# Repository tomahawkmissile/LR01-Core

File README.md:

# LR01-Core
Core controller of the LR-01 hybrid drone. Controls rotors, critical cooling, battery charge/discharge controllers and realtime sensors.

Aircraft specifications will be posted in another repository.
***Note: these files are about 95% complete.***

Features:
- TI AM3354 Arm Cortex-A8
- 512MB DDR3 (800MHz)
- HDMI out
- 1 Gigabit ethernet
- 2 USB 2.0
- 2 16GB eMCC flash
- 1 Application connector
- 12 layer PCB

***Note: this board may or may not function.***

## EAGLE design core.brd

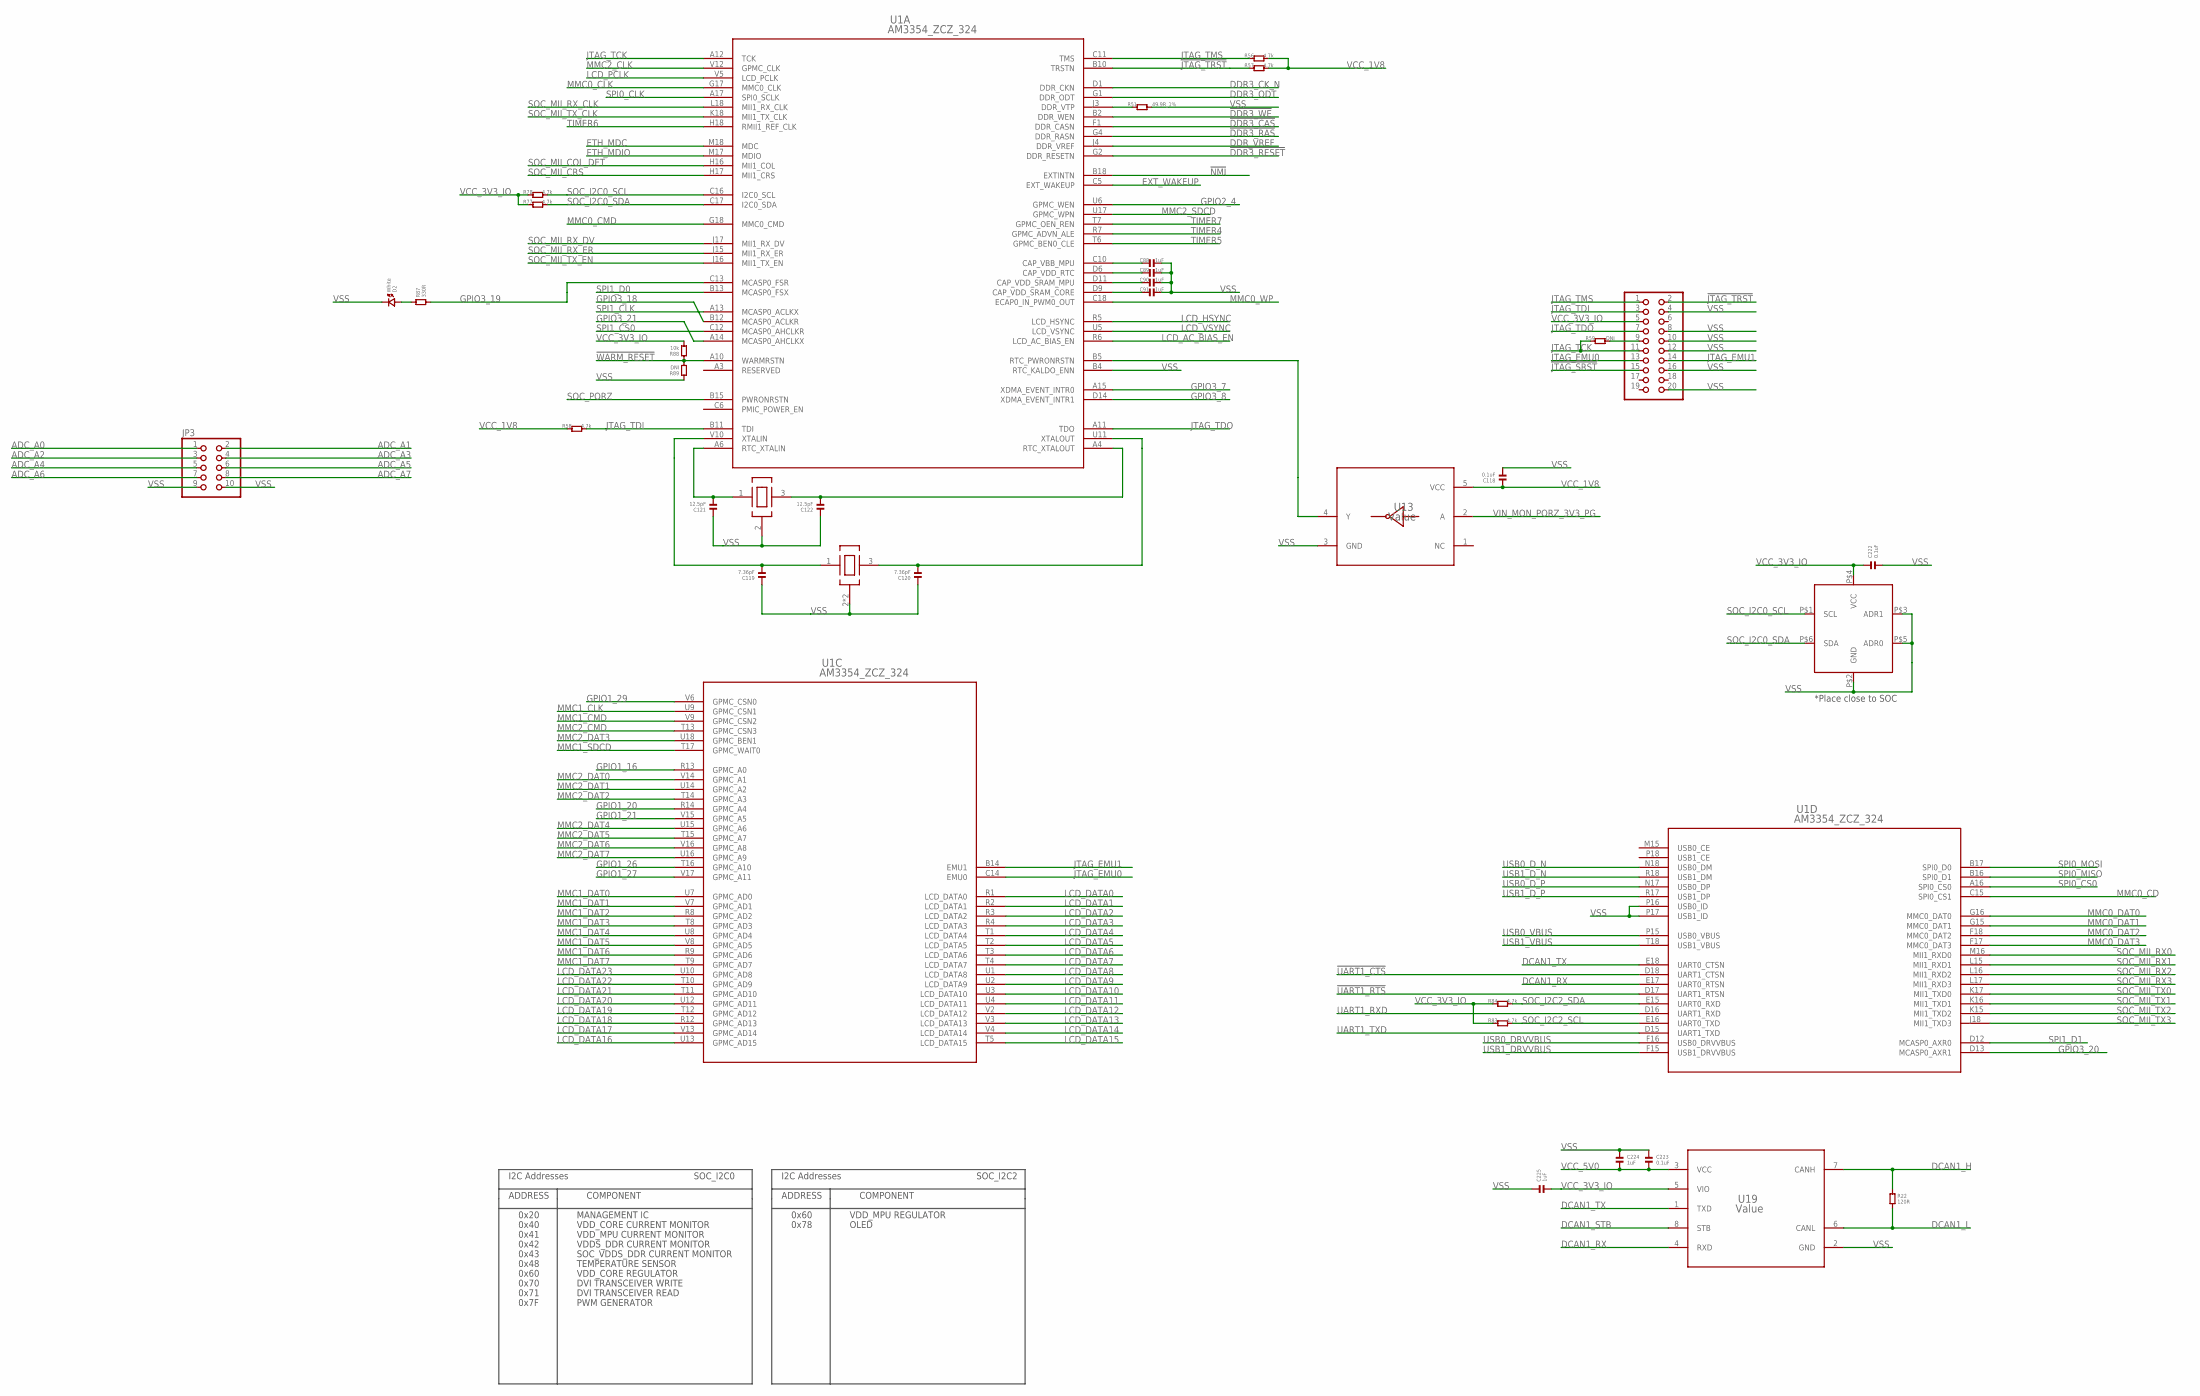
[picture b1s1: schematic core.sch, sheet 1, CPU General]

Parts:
C88, C89, C90, C91: 1uF; 0201
C118, C222, C223: 0.1uF; 0402
C119, C120: 7.36pF; 0402
C121, C122: 12.5pF; 0402
C224, C225: 1uF; 0402
D2: White; 0603.LED
JP1: PINHD-2X10; 2X10
JP3: PINHD-2X5; 2X05
R22: 120R; 0402
R51: 49.9R_1%; 0201
R56, R57, R58: 4.7k; 0603
R59, R89: DNI; 0402
R77, R78, R83, R84: 4.7k; 0402
R87: 330R; 0603
R88: 10k; 0402
U1: AM3354_ZCZ_324; ZCZ324
U13: Value; DCK0005A_N
U19: Value; D0008A_N
U$5: ECS-.327-12.5-1210B-N-TR; OSCCC120X100X35
U$6: NX3225SA-26.000000MHZ-G3; OSCCC320X250X70
U$9: TMP100; SOT23-6

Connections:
!DDR3_CAS: U1.F1 (DDR_CASN); also elsewhere on the board
!DDR3_RAS: U1.G4 (DDR_RASN); also elsewhere on the board
!DDR3_RESET: U1.G2 (DDR_RESETN); also elsewhere on the board
!DDR3_WE: U1.B2 (DDR_WEN); also elsewhere on the board
!JTAG_SRST: JP1.15
!JTAG_TRST: JP1.2, R57.1, U1.B10 (TRSTN); also elsewhere on the board
!NMI: U1.B18 (EXTINTN); also elsewhere on the board
!UART1_CTS: U1.D18 (UART1_CTSN); also elsewhere on the board
!UART1_RTS: U1.D17 (UART1_RTSN); also elsewhere on the board
!WARM_RESET: R88.1, R89.2, U1.A10 (WARMRSTN); also elsewhere on the board
ADC_A0: JP3.1; also elsewhere on the board
ADC_A1: JP3.2; also elsewhere on the board
ADC_A2: JP3.3; also elsewhere on the board
ADC_A3: JP3.4; also elsewhere on the board
ADC_A4: JP3.5; also elsewhere on the board
ADC_A5: JP3.6; also elsewhere on the board
ADC_A6: JP3.7; also elsewhere on the board
ADC_A7: JP3.8; also elsewhere on the board
DCAN1_H: R22.1, U19.7 (CANH); also elsewhere on the board
DCAN1_L: R22.2, U19.6 (CANL); also elsewhere on the board
DCAN1_RX: U1.E17 (UART0_RTSN), U19.4 (RXD)
DCAN1_STB: U19.8 (STB); also elsewhere on the board
DCAN1_TX: U1.E18 (UART0_CTSN), U19.1 (TXD)
DDR3_CK_N: U1.D1 (DDR_CKN); also elsewhere on the board
DDR3_ODT: U1.G1 (DDR_ODT); also elsewhere on the board
DDR_VREF: U1.J4 (DDR_VREF); also elsewhere on the board
ETH_MDC: U1.M18 (MDC); also elsewhere on the board
ETH_MDIO: U1.M17 (MDIO); also elsewhere on the board
EXT_WAKEUP: U1.C5 (EXT_WAKEUP); also elsewhere on the board
GPIO1_16: U1.R13 (GPMC_A0); also elsewhere on the board
GPIO1_20: U1.R14 (GPMC_A4); also elsewhere on the board
GPIO1_21: U1.V15 (GPMC_A5); also elsewhere on the board
GPIO1_26: U1.T16 (GPMC_A10); also elsewhere on the board
GPIO1_27: U1.V17 (GPMC_A11); also elsewhere on the board
GPIO1_29: U1.V6 (GPMC_CSN0); also elsewhere on the board
GPIO2_4: U1.U6 (GPMC_WEN); also elsewhere on the board
GPIO3_7: U1.A15 (XDMA_EVENT_INTR0); also elsewhere on the board
GPIO3_8: U1.D14 (XDMA_EVENT_INTR1); also elsewhere on the board
GPIO3_18: U1.B12 (MCASP0_ACLKR); also elsewhere on the board
GPIO3_19: R87.2, U1.C13 (MCASP0_FSR); also elsewhere on the board
GPIO3_20: U1.D13 (MCASP0_AXR1); also elsewhere on the board
GPIO3_21: U1.A14 (MCASP0_AHCLKX); also elsewhere on the board
JTAG_EMU0: JP1.13, U1.C14 (EMU0)
JTAG_EMU1: JP1.14, U1.B14 (EMU1)
JTAG_TCK: JP1.11, R59.1, U1.A12 (TCK)
JTAG_TDI: JP1.3, R58.2, U1.B11 (TDI)
JTAG_TDO: JP1.7, U1.A11 (TDO)
JTAG_TMS: JP1.1, R56.1, U1.C11 (TMS)
LCD_AC_BIAS_EN: U1.R6 (LCD_AC_BIAS_EN); also elsewhere on the board
LCD_DATA0: U1.R1 (LCD_DATA0); also elsewhere on the board
LCD_DATA1: U1.R2 (LCD_DATA1); also elsewhere on the board
LCD_DATA2: U1.R3 (LCD_DATA2); also elsewhere on the board
LCD_DATA3: U1.R4 (LCD_DATA3); also elsewhere on the board
LCD_DATA4: U1.T1 (LCD_DATA4); also elsewhere on the board
LCD_DATA5: U1.T2 (LCD_DATA5); also elsewhere on the board
LCD_DATA6: U1.T3 (LCD_DATA6); also elsewhere on the board
LCD_DATA7: U1.T4 (LCD_DATA7); also elsewhere on the board
LCD_DATA8: U1.U1 (LCD_DATA8); also elsewhere on the board
LCD_DATA9: U1.U2 (LCD_DATA9); also elsewhere on the board
LCD_DATA10: U1.U3 (LCD_DATA10); also elsewhere on the board
LCD_DATA11: U1.U4 (LCD_DATA11); also elsewhere on the board
LCD_DATA12: U1.V2 (LCD_DATA12); also elsewhere on the board
LCD_DATA13: U1.V3 (LCD_DATA13); also elsewhere on the board
LCD_DATA14: U1.V4 (LCD_DATA14); also elsewhere on the board
LCD_DATA15: U1.T5 (LCD_DATA15); also elsewhere on the board
LCD_DATA16: U1.U13 (GPMC_AD15); also elsewhere on the board
LCD_DATA17: U1.V13 (GPMC_AD14); also elsewhere on the board
LCD_DATA18: U1.R12 (GPMC_AD13); also elsewhere on the board
LCD_DATA19: U1.T12 (GPMC_AD12); also elsewhere on the board
LCD_DATA20: U1.U12 (GPMC_AD11); also elsewhere on the board
LCD_DATA21: U1.T11 (GPMC_AD10); also elsewhere on the board
LCD_DATA22: U1.T10 (GPMC_AD9); also elsewhere on the board
LCD_DATA23: U1.U10 (GPMC_AD8); also elsewhere on the board
LCD_HSYNC: U1.R5 (LCD_HSYNC); also elsewhere on the board
LCD_PCLK: U1.V5 (LCD_PCLK); also elsewhere on the board
LCD_VSYNC: U1.U5 (LCD_VSYNC); also elsewhere on the board
MMC0_CD: U1.C15 (SPI0_CS1); also elsewhere on the board
MMC0_CLK: U1.G17 (MMC0_CLK); also elsewhere on the board
MMC0_CMD: U1.G18 (MMC0_CMD); also elsewhere on the board
MMC0_DAT0: U1.G16 (MMC0_DAT0); also elsewhere on the board
MMC0_DAT1: U1.G15 (MMC0_DAT1); also elsewhere on the board
MMC0_DAT2: U1.F18 (MMC0_DAT2); also elsewhere on the board
MMC0_DAT3: U1.F17 (MMC0_DAT3); also elsewhere on the board
MMC0_WP: U1.C18 (ECAP0_IN_PWM0_OUT); also elsewhere on the board
MMC1_CLK: U1.U9 (GPMC_CSN1); also elsewhere on the board
MMC1_CMD: U1.V9 (GPMC_CSN2); also elsewhere on the board
MMC1_DAT0: U1.U7 (GPMC_AD0); also elsewhere on the board
MMC1_DAT1: U1.V7 (GPMC_AD1); also elsewhere on the board
MMC1_DAT2: U1.R8 (GPMC_AD2); also elsewhere on the board
MMC1_DAT3: U1.T8 (GPMC_AD3); also elsewhere on the board
MMC1_DAT4: U1.U8 (GPMC_AD4); also elsewhere on the board
MMC1_DAT5: U1.V8 (GPMC_AD5); also elsewhere on the board
MMC1_DAT6: U1.R9 (GPMC_AD6); also elsewhere on the board
MMC1_DAT7: U1.T9 (GPMC_AD7); also elsewhere on the board
MMC1_SDCD: U1.T17 (GPMC_WAIT0)
MMC2_CLK: U1.V12 (GPMC_CLK); also elsewhere on the board
MMC2_CMD: U1.T13 (GPMC_CSN3); also elsewhere on the board
MMC2_DAT0: U1.V14 (GPMC_A1); also elsewhere on the board
MMC2_DAT1: U1.U14 (GPMC_A2); also elsewhere on the board
MMC2_DAT2: U1.T14 (GPMC_A3); also elsewhere on the board
MMC2_DAT3: U1.U18 (GPMC_BEN1); also elsewhere on the board
MMC2_DAT4: U1.U15 (GPMC_A6); also elsewhere on the board
MMC2_DAT5: U1.T15 (GPMC_A7); also elsewhere on the board
MMC2_DAT6: U1.V16 (GPMC_A8); also elsewhere on the board
MMC2_DAT7: U1.U16 (GPMC_A9); also elsewhere on the board
MMC2_SDCD: U1.U17 (GPMC_WPN)
unnamed: JP1.9, R59.2
unnamed: C88.1, U1.C10 (CAP_VBB_MPU)
unnamed: C91.1, U1.D9 (CAP_VDD_SRAM_CORE)
unnamed: C90.1, U1.D11 (CAP_VDD_SRAM_MPU)
unnamed: U1.B5 (RTC_PWRONRSTN), U13.4 (Y)
unnamed: C121.2, U1.A6 (RTC_XTALIN), U$5.1 (XI)
unnamed: C122.2, U1.A4 (RTC_XTALOUT), U$5.3 (XO)
unnamed: C119.2, U1.V10 (XTALIN), U$6.1 (XI)
unnamed: C120.2, U1.U11 (XTALOUT), U$6.3 (XO)
unnamed: R51.1, U1.J3 (DDR_VTP)
unnamed: C89.1, U1.D6 (CAP_VDD_RTC)
unnamed: D2.P$1 (1), R87.1
SOC_I2C0_SCL: R78.2, U1.C16 (I2C0_SCL), U$9.P$1 (SCL); also elsewhere on the board
SOC_I2C0_SDA: R77.2, U1.C17 (I2C0_SDA), U$9.P$6 (SDA); also elsewhere on the board
SOC_I2C2_SCL: R83.2, U1.E16 (UART0_TXD); also elsewhere on the board
SOC_I2C2_SDA: R84.2, U1.E15 (UART0_RXD); also elsewhere on the board
SOC_MII_COL_DET: U1.H16 (MII1_COL); also elsewhere on the board
SOC_MII_CRS: U1.H17 (MII1_CRS); also elsewhere on the board
SOC_MII_RX0: U1.M16 (MII1_RXD0); also elsewhere on the board
SOC_MII_RX1: U1.L15 (MII1_RXD1); also elsewhere on the board
SOC_MII_RX2: U1.L16 (MII1_RXD2); also elsewhere on the board
SOC_MII_RX3: U1.L17 (MII1_RXD3); also elsewhere on the board
SOC_MII_RX_CLK: U1.L18 (MII1_RX_CLK); also elsewhere on the board
SOC_MII_RX_DV: U1.J17 (MII1_RX_DV); also elsewhere on the board
SOC_MII_RX_ER: U1.J15 (MII1_RX_ER); also elsewhere on the board
SOC_MII_TX0: U1.K17 (MII1_TXD0); also elsewhere on the board
SOC_MII_TX1: U1.K16 (MII1_TXD1); also elsewhere on the board
SOC_MII_TX2: U1.K15 (MII1_TXD2); also elsewhere on the board
SOC_MII_TX3: U1.J18 (MII1_TXD3); also elsewhere on the board
SOC_MII_TX_CLK: U1.K18 (MII1_TX_CLK); also elsewhere on the board
SOC_MII_TX_EN: U1.J16 (MII1_TX_EN); also elsewhere on the board
SOC_PORZ: U1.B15 (PWRONRSTN); also elsewhere on the board
SPI0_CLK: U1.A17 (SPI0_SCLK); also elsewhere on the board
SPI0_CS0: U1.A16 (SPI0_CS0); also elsewhere on the board
SPI0_MISO: U1.B16 (SPI0_D1); also elsewhere on the board
SPI0_MOSI: U1.B17 (SPI0_D0); also elsewhere on the board
SPI1_CLK: U1.A13 (MCASP0_ACLKX); also elsewhere on the board
SPI1_CS0: U1.C12 (MCASP0_AHCLKR); also elsewhere on the board
SPI1_D0: U1.B13 (MCASP0_FSX); also elsewhere on the board
SPI1_D1: U1.D12 (MCASP0_AXR0); also elsewhere on the board
TIMER4: U1.R7 (GPMC_ADVN_ALE); also elsewhere on the board
TIMER5: U1.T6 (GPMC_BEN0_CLE); also elsewhere on the board
TIMER6: U1.H18 (RMII1_REF_CLK); also elsewhere on the board
TIMER7: U1.T7 (GPMC_OEN_REN); also elsewhere on the board
UART1_RXD: U1.D16 (UART1_RXD); also elsewhere on the board
UART1_TXD: U1.D15 (UART1_TXD); also elsewhere on the board
USB0_DRVVBUS: U1.F16 (USB0_DRVVBUS); also elsewhere on the board
USB0_D_N: U1.N18 (USB0_DM); also elsewhere on the board
USB0_D_P: U1.N17 (USB0_DP); also elsewhere on the board
USB0_VBUS: U1.P15 (USB0_VBUS); also elsewhere on the board
USB1_DRVVBUS: U1.F15 (USB1_DRVVBUS); also elsewhere on the board
USB1_D_N: U1.R18 (USB1_DM); also elsewhere on the board
USB1_D_P: U1.R17 (USB1_DP); also elsewhere on the board
USB1_VBUS: U1.T18 (USB1_VBUS); also elsewhere on the board
VCC_1V8: C118.1, R56.2, R57.2, R58.1, U13.5 (VCC); also elsewhere on the board
VCC_3V3_IO: C222.1, C225.2, JP1.5, R77.1, R78.1, R83.1, R84.1, R88.2, U19.5 (VIO), U$9.P$4 (VCC); also elsewhere on the board
VCC_5V0: C223.2, C224.2, U19.3 (VCC); also elsewhere on the board
VIN_MON_PORZ_3V3_PG: U13.2 (A); also elsewhere on the board
VPP: U1.M5 (VPP)
VSS: C88.2, C89.2, C90.2, C91.2, C118.2, C119.1, C120.1, C121.1, C122.1, C222.2, C223.1, C224.1, C225.1, D2.P$2 (2), JP1.4, JP1.8, JP1.10, JP1.12, JP1.16, JP1.20, JP3.9, JP3.10, R51.2, R89.1, U1.B4 (RTC_KALDO_ENN), U1.P16 (USB0_ID), U1.P17 (USB1_ID), U13.3 (GND), U19.2 (GND), U$5.2 (VSS), U$6.2 (VSS), U$6.4 (VSS), U$9.P$2 (GND), U$9.P$3 (ADR1), U$9.P$5 (ADR0); also elsewhere on the board

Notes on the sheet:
I2C Addresses
0x20
MANAGEMENT IC
ADDRESS
COMPONENT
0x40
0x41
0x42
0x43
VDD_CORE CURRENT MONITOR
VDD_MPU CURRENT MONITOR
VDDS_DDR CURRENT MONITOR
SOC_VDDS_DDR CURRENT MONITOR
0x60
VDD_CORE REGULATOR
SOC_I2C0
VDD_MPU REGULATOR
SOC_I2C2
0x70
0x71
DVI TRANSCEIVER WRITE
DVI TRANSCEIVER READ
0x78
OLED
0x48
TEMPERATURE SENSOR
*Place close to SOC
0x7F
PWM GENERATOR

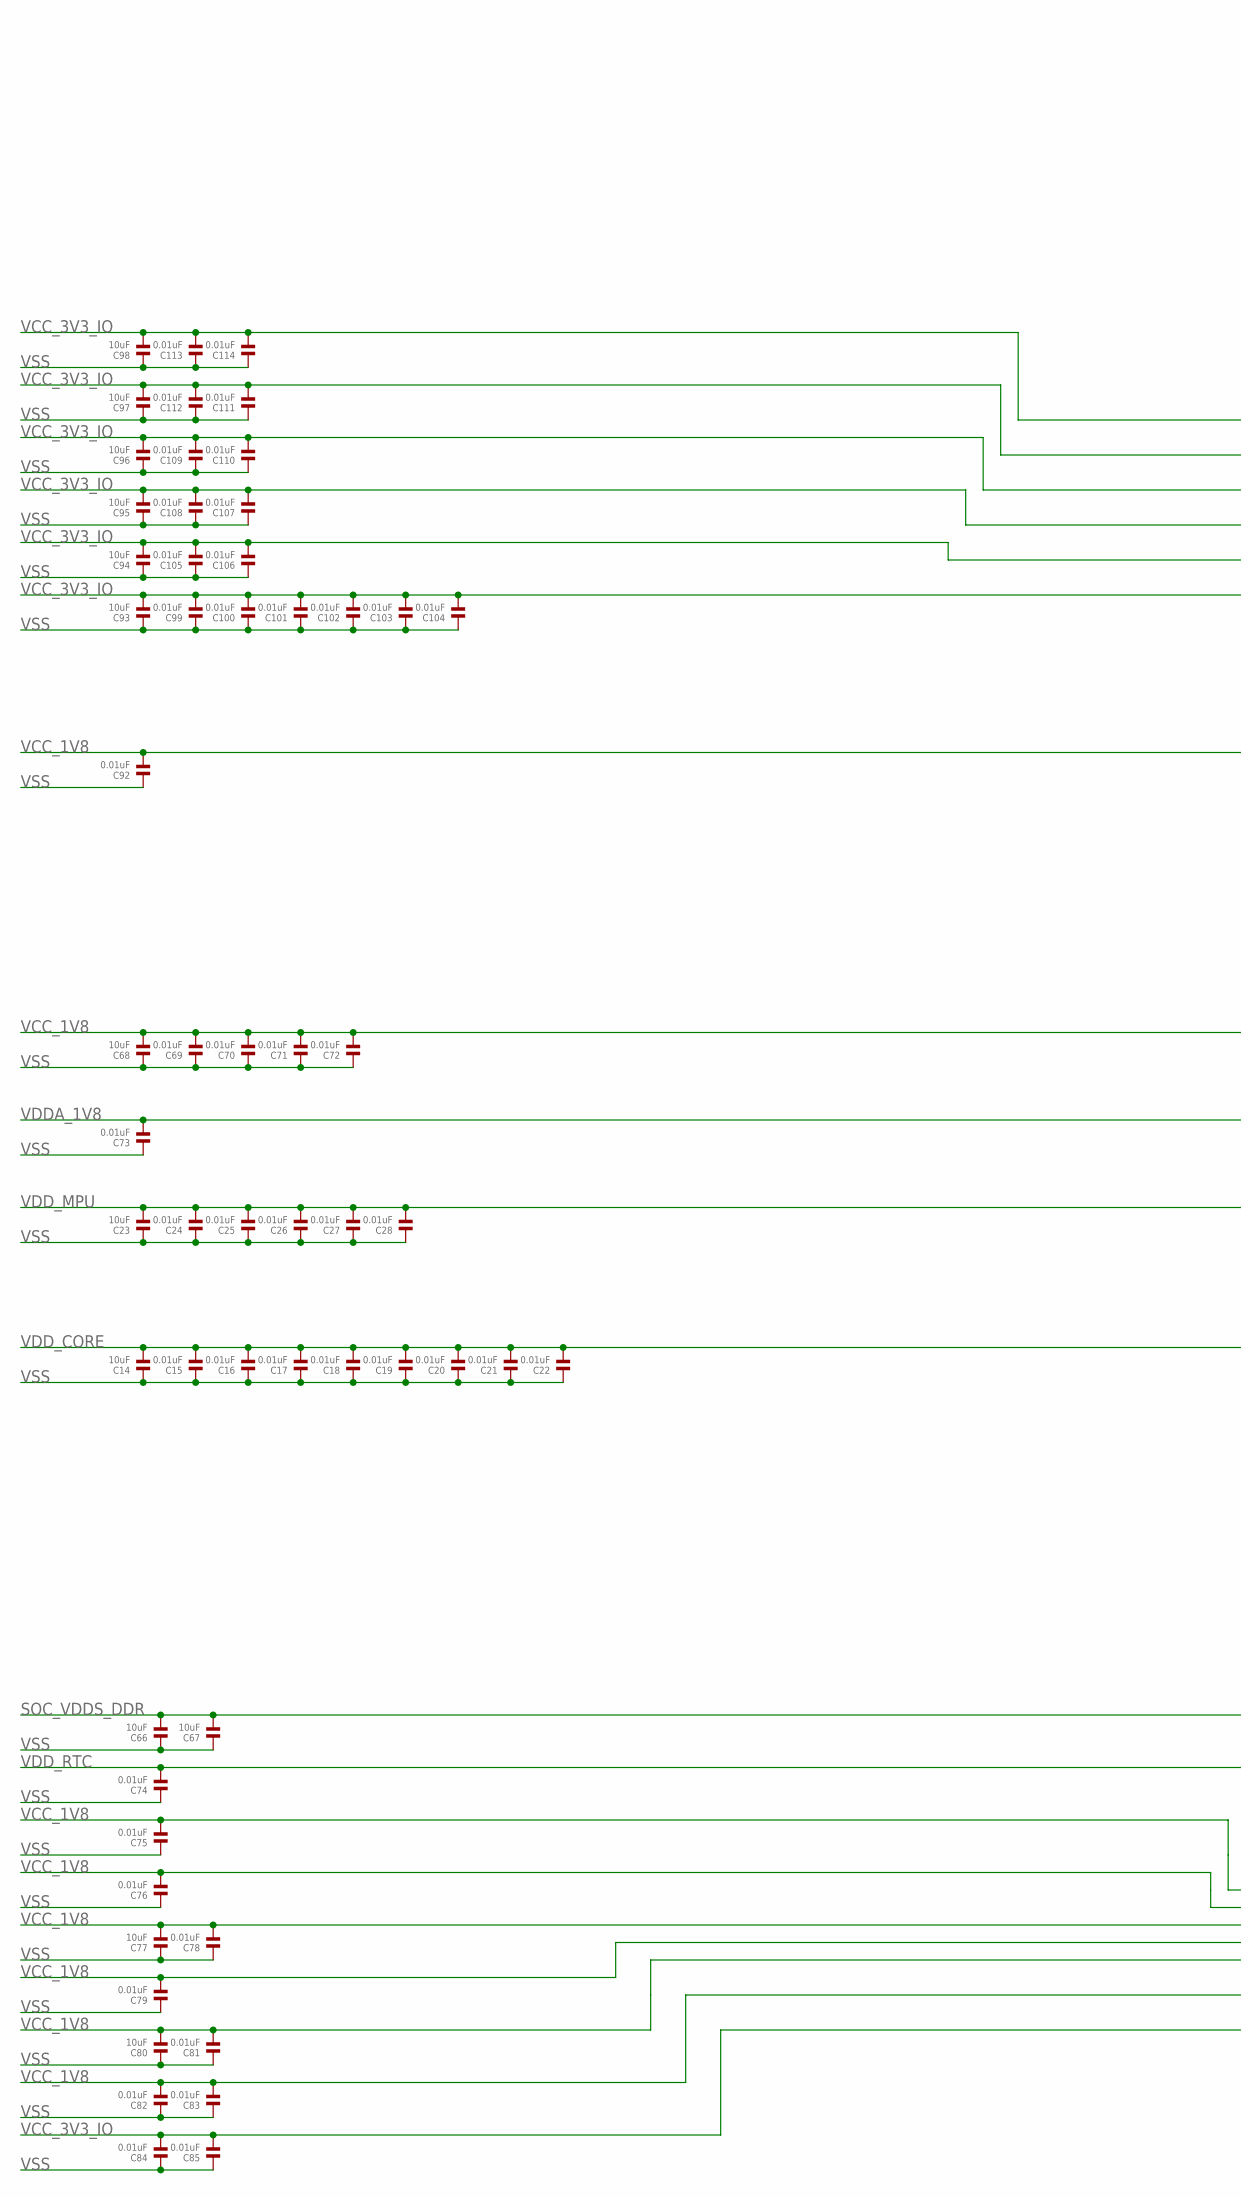
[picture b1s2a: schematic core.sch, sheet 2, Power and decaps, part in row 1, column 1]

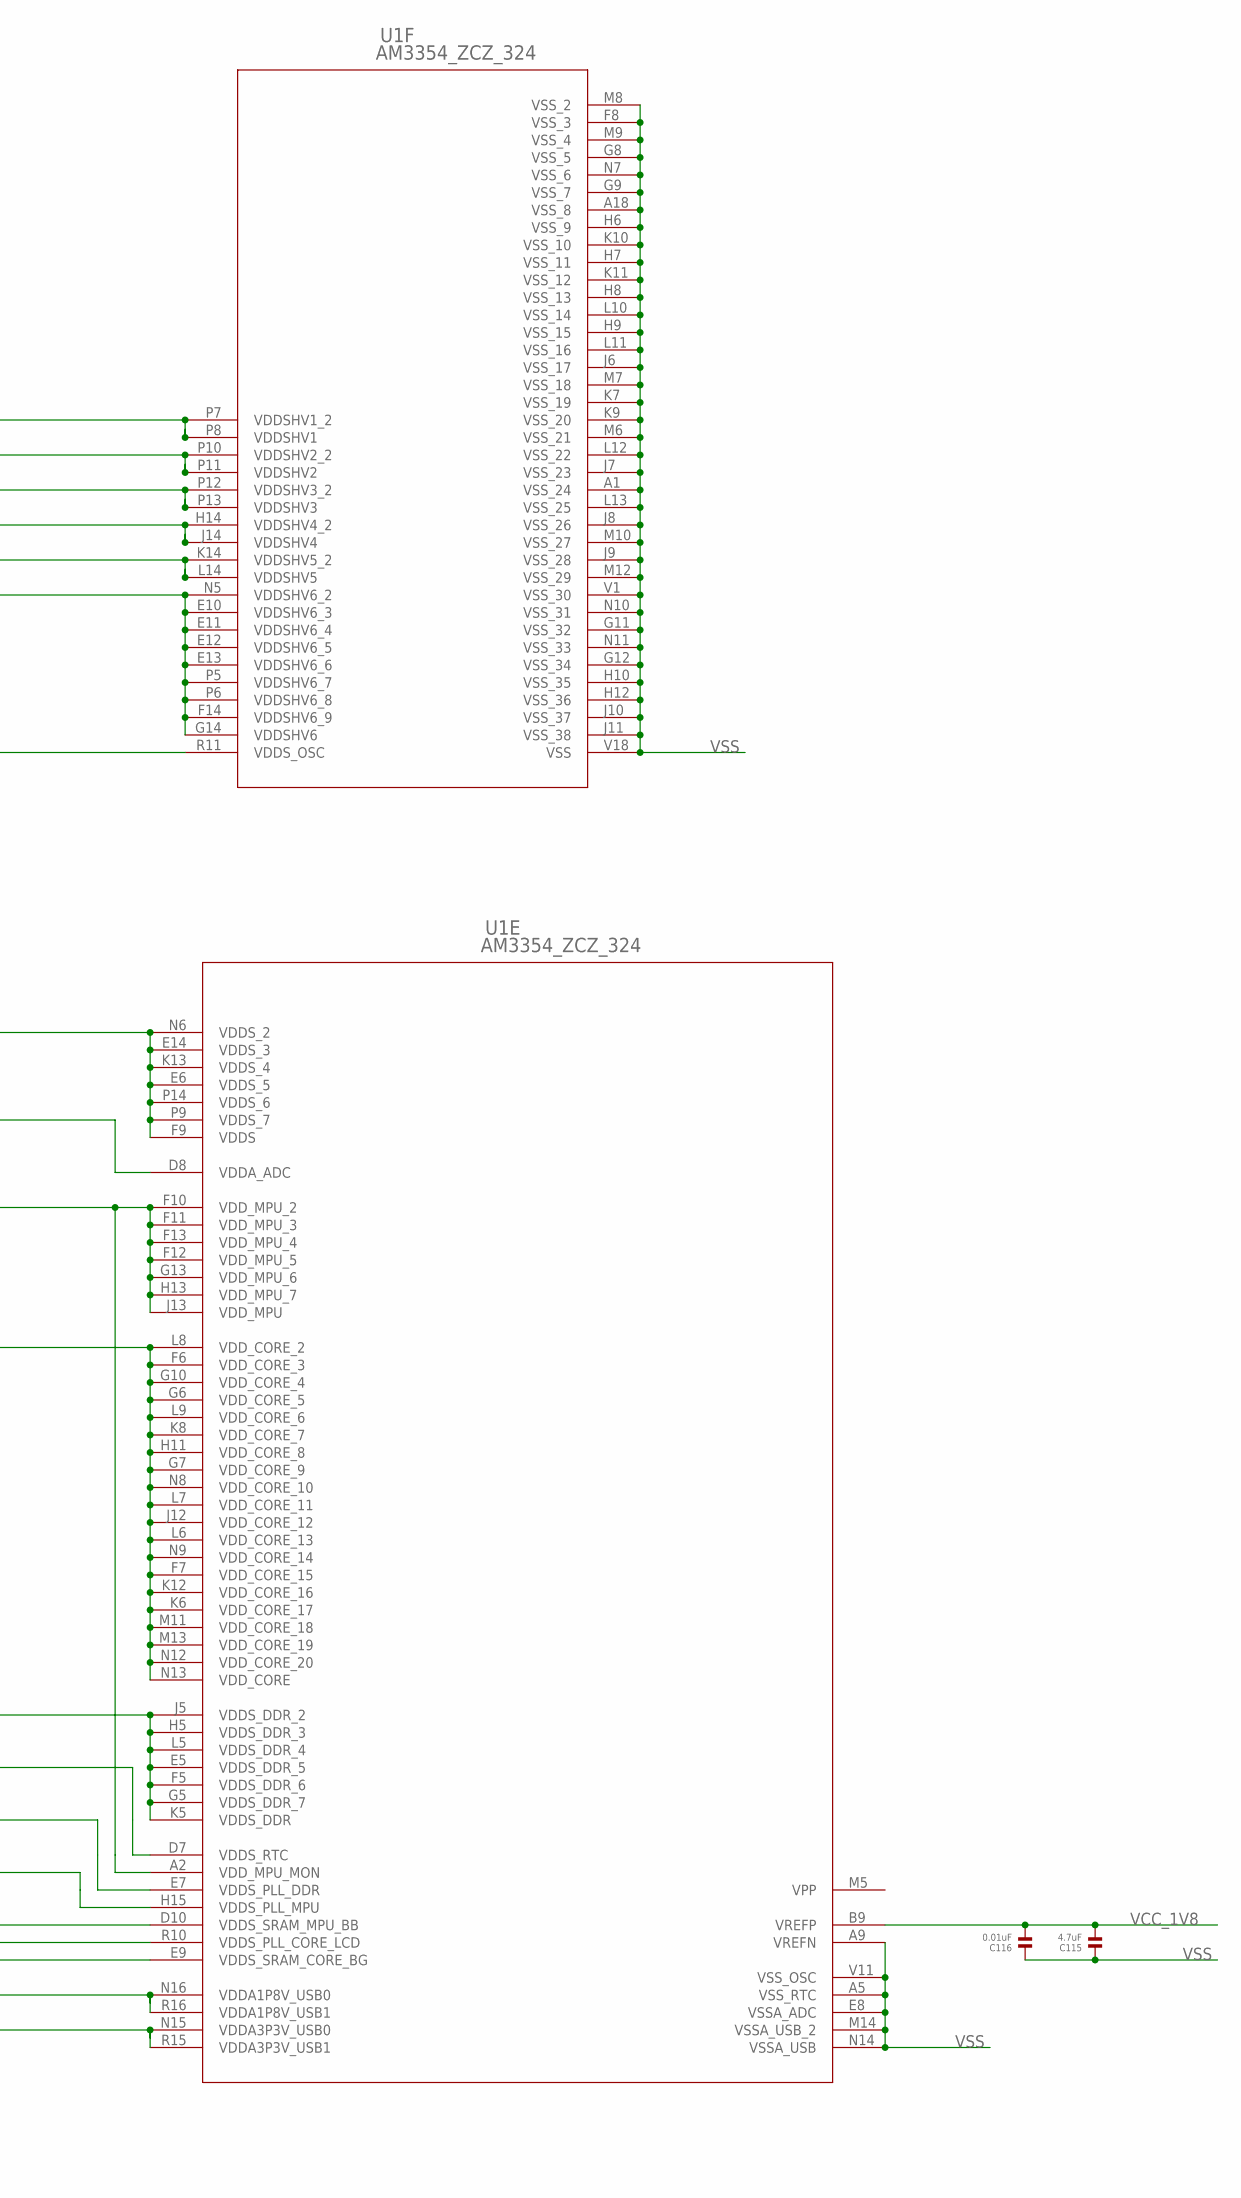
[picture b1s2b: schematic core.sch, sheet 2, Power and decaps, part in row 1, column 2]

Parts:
C14, C23, C66, C67, C68, C77, C80, C93, C94, C95, C96, C97, C98: 10uF; 0402
C15, C16, C17, C18, C19, C20, C21, C22, C24, C25, C26, C27, C28, C69, C70, C71, C72, C73, C74, C75, C76, C78, C79, C81, C82, C83, C84, C85, C92, C99, C100, C101, C102, C103, C104, C105, C106, C107, C108, C109, C110, C111, C112, C113, C114, C116: 0.01uF; 0201
C115: 4.7uF; 0402
U1: AM3354_ZCZ_324; ZCZ324

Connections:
SOC_VDDS_DDR: C66.2, C67.2, U1.E5 (VDDS_DDR_5), U1.F5 (VDDS_DDR_6), U1.G5 (VDDS_DDR_7), U1.H5 (VDDS_DDR_3), U1.J5 (VDDS_DDR_2), U1.K5 (VDDS_DDR), U1.L5 (VDDS_DDR_4); also elsewhere on the board
VCC_1V8: C68.2, C69.2, C70.2, C71.2, C72.2, C75.2, C76.2, C77.2, C78.2, C79.2, C80.2, C81.2, C82.2, C83.2, C92.2, C115.2, C116.2, U1.B9 (VREFP), U1.D10 (VDDS_SRAM_MPU_BB), U1.E6 (VDDS_5), U1.E7 (VDDS_PLL_DDR), U1.E9 (VDDS_SRAM_CORE_BG), U1.E14 (VDDS_3), U1.F9 (VDDS), U1.H15 (VDDS_PLL_MPU), U1.K13 (VDDS_4), U1.N6 (VDDS_2), U1.N16 (VDDA1P8V_USB0), U1.P9 (VDDS_7), U1.P14 (VDDS_6), U1.R10 (VDDS_PLL_CORE_LCD), U1.R11 (VDDS_OSC), U1.R16 (VDDA1P8V_USB1); also elsewhere on the board
VCC_3V3_IO: C84.2, C85.2, C93.2, C94.2, C95.2, C96.2, C97.2, C98.2, C99.2, C100.2, C101.2, C102.2, C103.2, C104.2, C105.2, C106.2, C107.2, C108.2, C109.2, C110.2, C111.2, C112.2, C113.2, C114.2, U1.E10 (VDDSHV6_3), U1.E11 (VDDSHV6_4), U1.E12 (VDDSHV6_5), U1.E13 (VDDSHV6_6), U1.F14 (VDDSHV6_9), U1.G14 (VDDSHV6), U1.H14 (VDDSHV4_2), U1.J14 (VDDSHV4), U1.K14 (VDDSHV5_2), U1.L14 (VDDSHV5), U1.N5 (VDDSHV6_2), U1.N15 (VDDA3P3V_USB0), U1.P5 (VDDSHV6_7), U1.P6 (VDDSHV6_8), U1.P7 (VDDSHV1_2), U1.P8 (VDDSHV1), U1.P10 (VDDSHV2_2), U1.P11 (VDDSHV2), U1.P12 (VDDSHV3_2), U1.P13 (VDDSHV3), U1.R15 (VDDA3P3V_USB1); also elsewhere on the board
VDDA_1V8: C73.2, U1.D8 (VDDA_ADC); also elsewhere on the board
VDD_CORE: C14.2, C15.2, C16.2, C17.2, C18.2, C19.2, C20.2, C21.2, C22.2, U1.F6 (VDD_CORE_3), U1.F7 (VDD_CORE_15), U1.G6 (VDD_CORE_5), U1.G7 (VDD_CORE_9), U1.G10 (VDD_CORE_4), U1.H11 (VDD_CORE_8), U1.J12 (VDD_CORE_12), U1.K6 (VDD_CORE_17), U1.K8 (VDD_CORE_7), U1.K12 (VDD_CORE_16), U1.L6 (VDD_CORE_13), U1.L7 (VDD_CORE_11), U1.L8 (VDD_CORE_2), U1.L9 (VDD_CORE_6), U1.M11 (VDD_CORE_18), U1.M13 (VDD_CORE_19), U1.N8 (VDD_CORE_10), U1.N9 (VDD_CORE_14), U1.N12 (VDD_CORE_20), U1.N13 (VDD_CORE); also elsewhere on the board
VDD_MPU: C23.2, C24.2, C25.2, C26.2, C27.2, C28.2, U1.A2 (VDD_MPU_MON), U1.F10 (VDD_MPU_2), U1.F11 (VDD_MPU_3), U1.F12 (VDD_MPU_5), U1.F13 (VDD_MPU_4), U1.G13 (VDD_MPU_6), U1.H13 (VDD_MPU_7), U1.J13 (VDD_MPU); also elsewhere on the board
VDD_RTC: C74.2, U1.D7 (VDDS_RTC); also elsewhere on the board
VPP: U1.M5 (VPP)
VSS: C14.1, C15.1, C16.1, C17.1, C18.1, C19.1, C20.1, C21.1, C22.1, C23.1, C24.1, C25.1, C26.1, C27.1, C28.1, C66.1, C67.1, C68.1, C69.1, C70.1, C71.1, C72.1, C73.1, C74.1, C75.1, C76.1, C77.1, C78.1, C79.1, C80.1, C81.1, C82.1, C83.1, C84.1, C85.1, C92.1, C93.1, C94.1, C95.1, C96.1, C97.1, C98.1, C99.1, C100.1, C101.1, C102.1, C103.1, C104.1, C105.1, C106.1, C107.1, C108.1, C109.1, C110.1, C111.1, C112.1, C113.1, C114.1, C115.1, C116.1, U1.A1 (VSS_24), U1.A5 (VSS_RTC), U1.A9 (VREFN), U1.A18 (VSS_8), U1.E8 (VSSA_ADC), U1.F8 (VSS_3), U1.G8 (VSS_5), U1.G9 (VSS_7), U1.G11 (VSS_32), U1.G12 (VSS_34), U1.H6 (VSS_9), U1.H7 (VSS_11), U1.H8 (VSS_13), U1.H9 (VSS_15), U1.H10 (VSS_35), U1.H12 (VSS_36), U1.J6 (VSS_17), U1.J7 (VSS_23), U1.J8 (VSS_26), U1.J9 (VSS_28), U1.J10 (VSS_37), U1.J11 (VSS_38), U1.K7 (VSS_19), U1.K9 (VSS_20), U1.K10 (VSS_10), U1.K11 (VSS_12), U1.L10 (VSS_14), U1.L11 (VSS_16), U1.L12 (VSS_22), U1.L13 (VSS_25), U1.M6 (VSS_21), U1.M7 (VSS_18), U1.M8 (VSS_2), U1.M9 (VSS_4), U1.M10 (VSS_27), U1.M12 (VSS_29), U1.M14 (VSSA_USB_2), U1.N7 (VSS_6), U1.N10 (VSS_31), U1.N11 (VSS_33), U1.N14 (VSSA_USB), U1.V1 (VSS_30), U1.V11 (VSS_OSC), U1.V18 (VSS); also elsewhere on the board
